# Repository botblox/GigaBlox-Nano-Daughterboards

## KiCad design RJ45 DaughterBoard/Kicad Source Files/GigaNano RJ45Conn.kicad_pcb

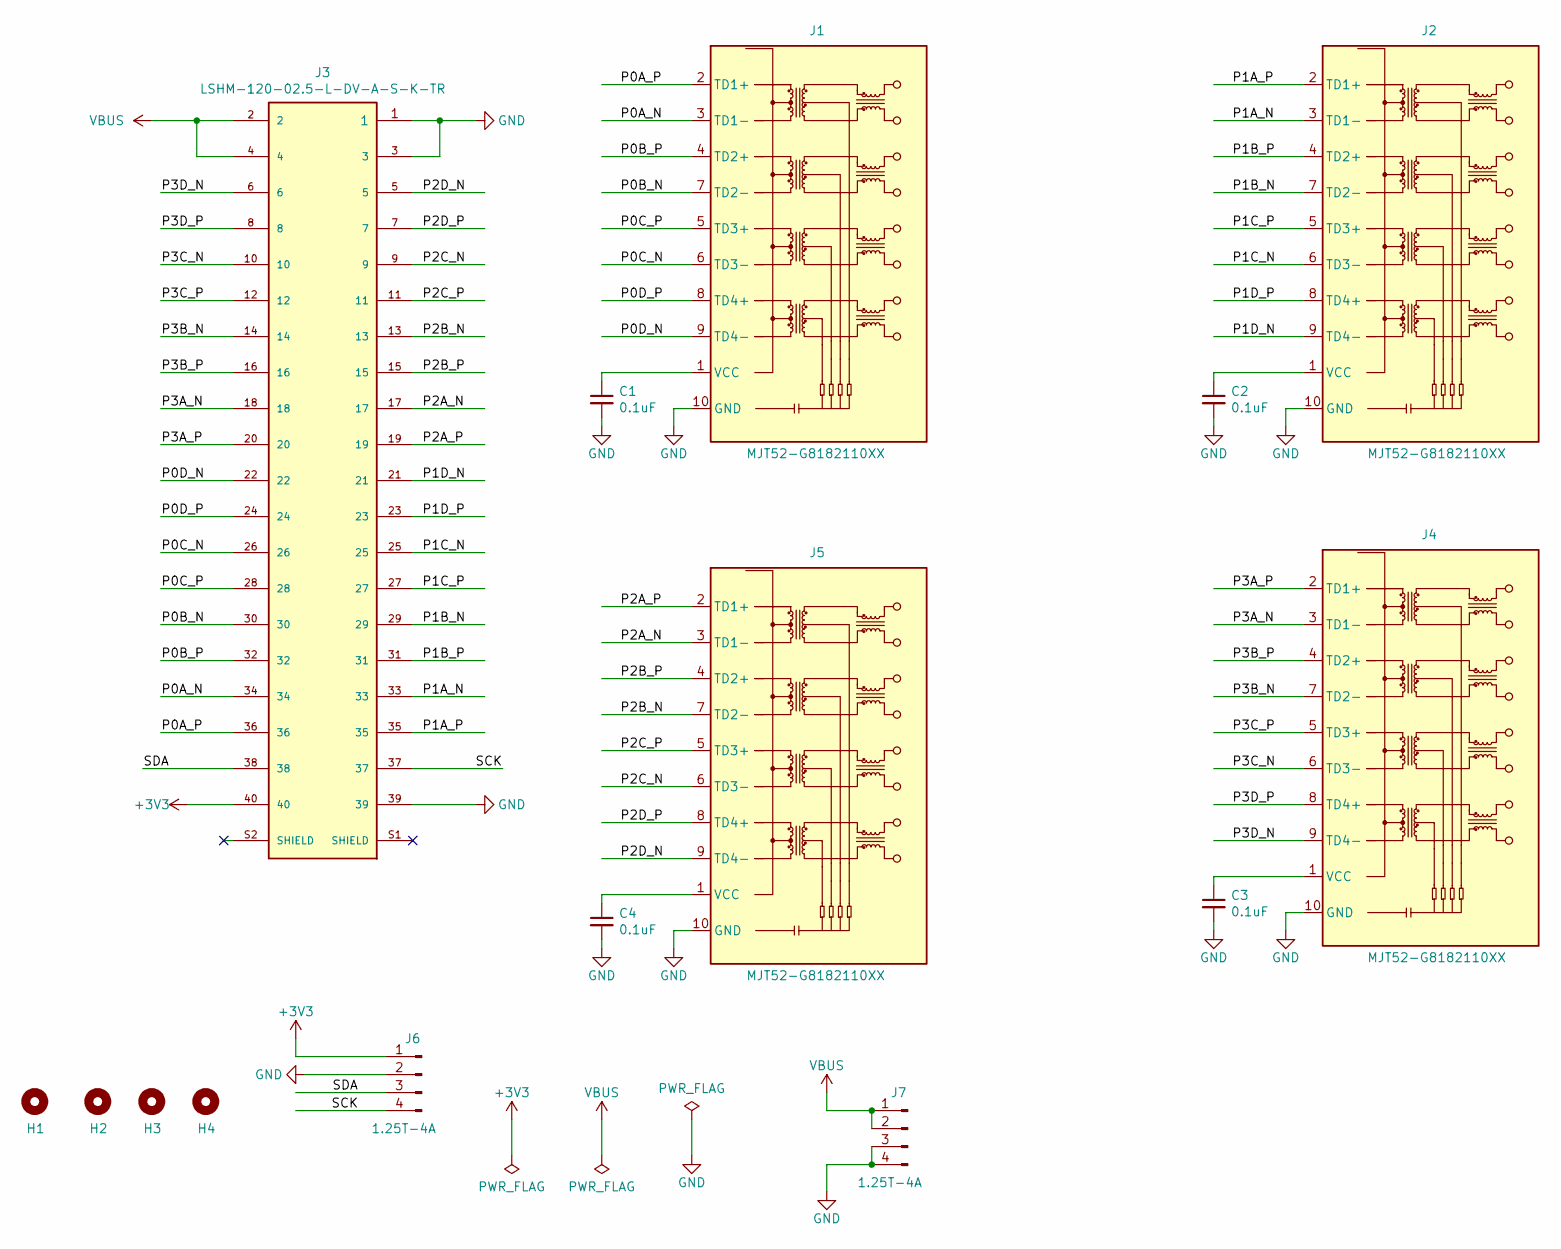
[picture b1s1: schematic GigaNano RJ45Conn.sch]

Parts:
C1, C2, C3, C4: 0.1uF; C_0402_1005Metric; MPN CC0402KRX7R9BB104; LCSC Part# C131394
H1, H2, H3, H4: MountingHole; MountingHole_2.2mm_M2_ISO7380_Pad; MPN DNP; LCSC Part# DNP
J1, J2, J4, J5: MJT52-G8182110XX; RJ45_Wayconn_MJT52-G8182110XX_Vertical; MPN MJT52-G8182110XX
J3: LSHM-120-02.5-L-DV-A-S-K-TR; Samtec_LSHM-120-02.5-L-DV-A-S-TR_P0.50mm_Vertical; MPN LSHM-120-02.5-L-DV-A-S-K-TR
J6, J7: 1.25T-4A; Molex_PicoBlade_53047-0410_1x04_P1.25mm_Vertical; MPN 1.25T-4A; LCSC Part# C145972

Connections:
+3V3: J3.40, J6.1
/P0A_N: J1.3 (TD1-), J3.34
/P0A_P: J1.2 (TD1+), J3.36
/P0B_N: J1.7 (TD2-), J3.30
/P0B_P: J1.4 (TD2+), J3.32
/P0C_N: J1.6 (TD3-), J3.26
/P0C_P: J1.5 (TD3+), J3.28
/P0D_N: J1.9 (TD4-), J3.22
/P0D_P: J1.8 (TD4+), J3.24
/P1A_N: J2.3 (TD1-), J3.33
/P1A_P: J2.2 (TD1+), J3.35
/P1B_N: J2.7 (TD2-), J3.29
/P1B_P: J2.4 (TD2+), J3.31
/P1C_N: J2.6 (TD3-), J3.25
/P1C_P: J2.5 (TD3+), J3.27
/P1D_N: J2.9 (TD4-), J3.21
/P1D_P: J2.8 (TD4+), J3.23
/P2A_N: J3.17, J5.3 (TD1-)
/P2A_P: J3.19, J5.2 (TD1+)
/P2B_N: J3.13, J5.7 (TD2-)
/P2B_P: J3.15, J5.4 (TD2+)
/P2C_N: J3.9, J5.6 (TD3-)
/P2C_P: J3.11, J5.5 (TD3+)
/P2D_N: J3.5, J5.9 (TD4-)
/P2D_P: J3.7, J5.8 (TD4+)
/P3A_N: J3.18, J4.3 (TD1-)
/P3A_P: J3.20, J4.2 (TD1+)
/P3B_N: J3.14, J4.7 (TD2-)
/P3B_P: J3.16, J4.4 (TD2+)
/P3C_N: J3.10, J4.6 (TD3-)
/P3C_P: J3.12, J4.5 (TD3+)
/P3D_N: J3.6, J4.9 (TD4-)
/P3D_P: J3.8, J4.8 (TD4+)
/SCK: J3.37, J6.4
/SDA: J3.38, J6.3
GND: C1.2, C2.2, C3.2, C4.2, J1.10 (GND), J2.10 (GND), J3.1, J3.3, J3.39, J4.10 (GND), J5.10 (GND), J6.2, J7.3, J7.4
unnamed: C1.1, J1.1 (VCC)
unnamed: C2.1, J2.1 (VCC)
unnamed: C3.1, J4.1 (VCC)
unnamed: C4.1, J5.1 (VCC)
VBUS: J3.2, J3.4, J7.1, J7.2

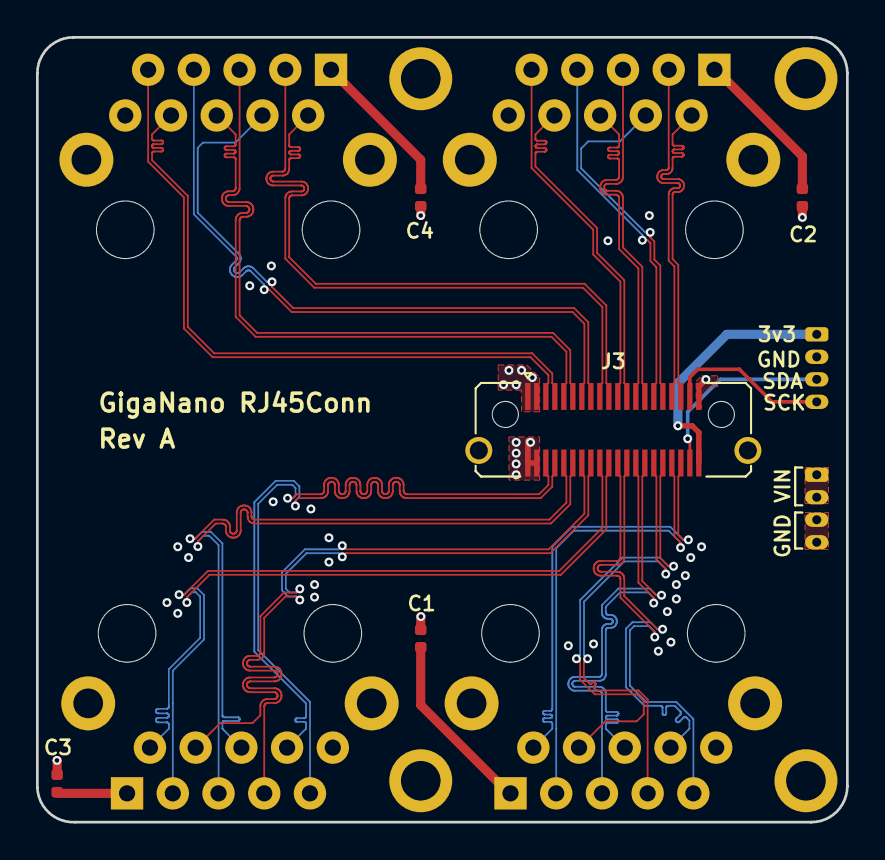
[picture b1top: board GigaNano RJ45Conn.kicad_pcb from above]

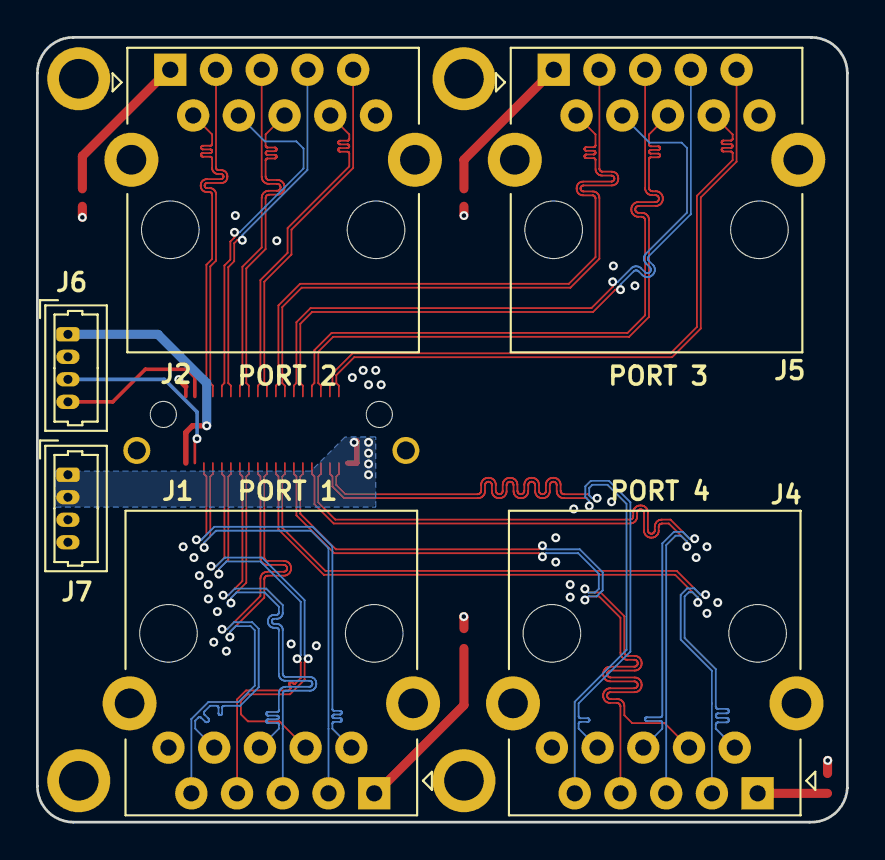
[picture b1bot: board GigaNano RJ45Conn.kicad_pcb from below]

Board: 4 copper layers, 45.0 x 43.6 mm, 15 parts (6 on the bottom side), 41 nets.

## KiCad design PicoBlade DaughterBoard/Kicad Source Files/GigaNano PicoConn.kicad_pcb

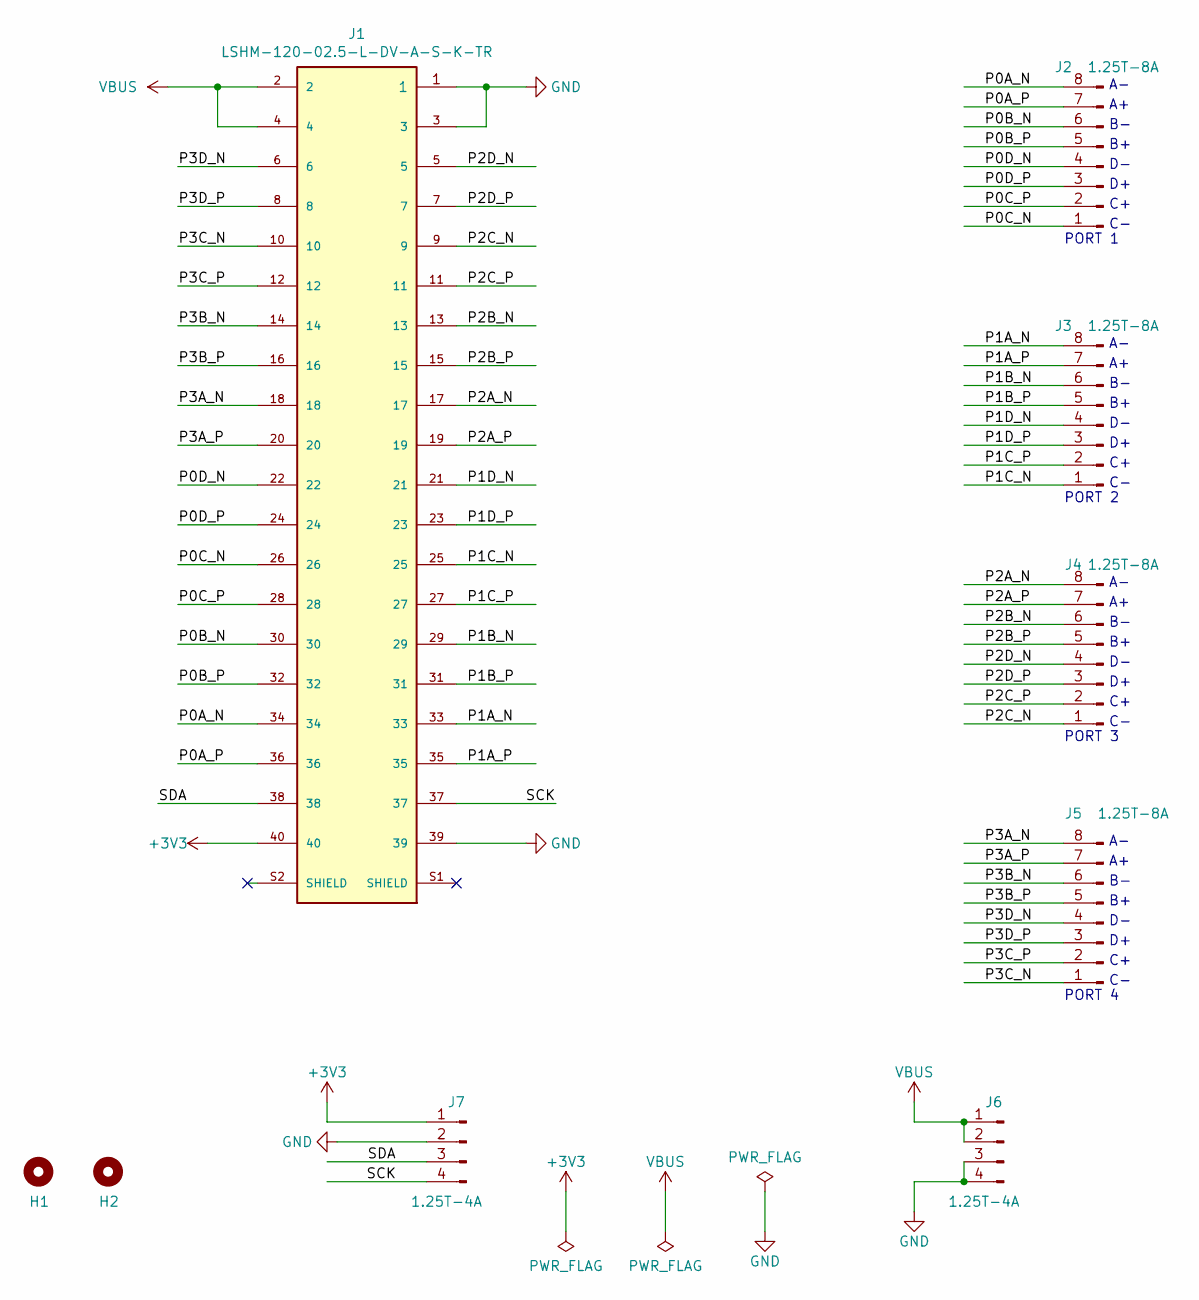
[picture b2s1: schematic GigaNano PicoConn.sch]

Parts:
H1, H2: MountingHole; MountingHole_2.2mm_M2_ISO7380_Pad
J1: LSHM-120-02.5-L-DV-A-S-K-TR; Samtec_LSHM-120-02.5-L-DV-A-S-TR_P0.50mm_Vertical; MPN LSHM-120-02.5-L-DV-A-S-K-TR
J2, J3, J4, J5: 1.25T-8A; Molex_PicoBlade_53047-0810_1x08_P1.25mm_Vertical; MPN 1.25T-8A; LCSC Part# C145976
J6, J7: 1.25T-4A; Molex_PicoBlade_53047-0410_1x04_P1.25mm_Vertical; MPN 1.25T-4A; LCSC Part# C145972

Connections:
+3V3: J1.40, J7.1
/P0A_N: J1.34, J2.8
/P0A_P: J1.36, J2.7
/P0B_N: J1.30, J2.6
/P0B_P: J1.32, J2.5
/P0C_N: J1.26, J2.1
/P0C_P: J1.28, J2.2
/P0D_N: J1.22, J2.4
/P0D_P: J1.24, J2.3
/P1A_N: J1.33, J3.8
/P1A_P: J1.35, J3.7
/P1B_N: J1.29, J3.6
/P1B_P: J1.31, J3.5
/P1C_N: J1.25, J3.1
/P1C_P: J1.27, J3.2
/P1D_N: J1.21, J3.4
/P1D_P: J1.23, J3.3
/P2A_N: J1.17, J4.8
/P2A_P: J1.19, J4.7
/P2B_N: J1.13, J4.6
/P2B_P: J1.15, J4.5
/P2C_N: J1.9, J4.1
/P2C_P: J1.11, J4.2
/P2D_N: J1.5, J4.4
/P2D_P: J1.7, J4.3
/P3A_N: J1.18, J5.8
/P3A_P: J1.20, J5.7
/P3B_N: J1.14, J5.6
/P3B_P: J1.16, J5.5
/P3C_N: J1.10, J5.1
/P3C_P: J1.12, J5.2
/P3D_N: J1.6, J5.4
/P3D_P: J1.8, J5.3
/SCK: J1.37, J7.4
/SDA: J1.38, J7.3
GND: J1.1, J1.3, J1.39, J6.3, J6.4, J7.2
VBUS: J1.2, J1.4, J6.1, J6.2

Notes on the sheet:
PORT 1
PORT 2
PORT 4
PORT 3

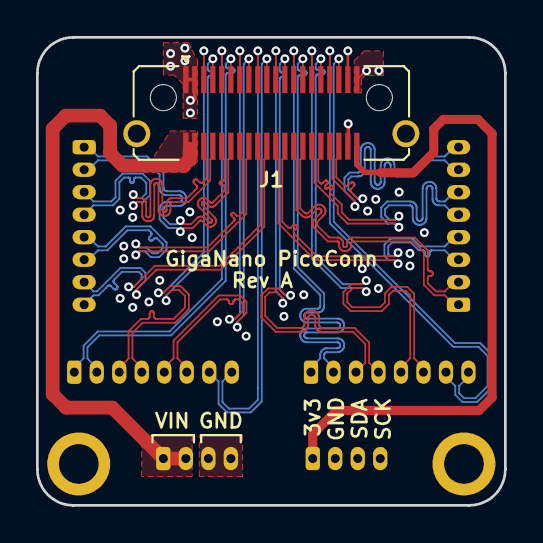
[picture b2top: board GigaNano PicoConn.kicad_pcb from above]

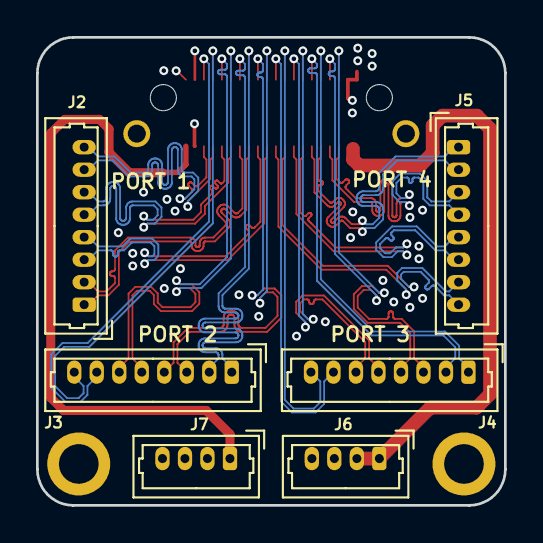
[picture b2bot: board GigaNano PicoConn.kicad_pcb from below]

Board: 4 copper layers, 26.0 x 26.0 mm, 9 parts (6 on the bottom side), 37 nets.

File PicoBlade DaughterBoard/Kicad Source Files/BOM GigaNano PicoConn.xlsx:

No | Ref | Value | Description | Manufacturer | Manufacturer Part Number | LCSC Part# | Supplier 1 | Footprint | Quantity | Price ($)
1 | J1, | LSHM-120-02.5-L-DV-A-S-K-TR | CONN SELF-MATE 40POS SMD GOLD | Samtec Inc. | LSHM-120-02.5-L-DV-A-S-K-TR |  | Mouser | GigaBloxTLE:Samtec_LSHM-120-02.5-L-DV-A-S-TR_P0.50mm_Vertical | 1 | 5.2629999999999999
2 | J2, J3, J4, J5, | 1.25T-8A | MX1.25 Header Male Blade 0.049"(1.25mm) 8 Through Hole,P=1.25mm Wire To Board /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 | BOOMELE | 1.25T-8A | C145976 | LCSC | Connector_Molex:Molex_PicoBlade_53047-0810_1x08_P1.25mm_Vertical | 4 | 0.03
3 | J6, J7, | 1.25T-4A | MX1.25 Header Male Pin 0.049"(1.25mm) 4 Through Hole,P=1.25mm Wire To Board / W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 | BOOMELE | 1.25T-4A | C145972 | LCSC | Connector_Molex:Molex_PicoBlade_53047-0410_1x04_P1.25mm_Vertical | 2 | 1.4E-2

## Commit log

2021-06-13 Added files for picoblade and RJ45 daughterboards
